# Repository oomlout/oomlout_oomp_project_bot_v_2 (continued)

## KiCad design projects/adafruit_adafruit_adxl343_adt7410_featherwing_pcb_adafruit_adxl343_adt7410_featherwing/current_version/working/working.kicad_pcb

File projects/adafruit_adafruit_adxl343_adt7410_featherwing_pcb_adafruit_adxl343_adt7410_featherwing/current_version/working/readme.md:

# adafruit_adxl343_adt7410_featherwing_pcb
 
## summary 
* id: adafruit_adafruit_adxl343_adt7410_featherwing_pcb_adafruit_adxl343_adt7410_featherwing
* user: adafruit
* name: adafruit_adxl343_adt7410_featherwing_pcb
* board: adafruit_adxl343_adt7410_featherwing
* repo: https://github.com/adafruit/Adafruit-ADXL343-ADT7410-Featherwing-PCB

* src_file_repo_sch: 
* src_file_repo_sch_link: https://github.com/adafruit/Adafruit-ADXL343-ADT7410-Featherwing-PCB/tree/master/
* full details link: https://github.com/oomlout/oomlout_oomp_project_bot_v_2/tree/main/projects/adafruit_adafruit_adxl343_adt7410_featherwing_pcb_adafruit_adxl343_adt7410_featherwing/current_version/working  

## schematic  
  
[schematic (pdf)](working_schematic.pdf) 

## pcb  

[board (pdf)](working.pdf)  

## working_bom
| Id | Designator | Footprint | Quantity | Designation | Supplier and ref |  | None | 
| --- | --- | --- | --- | --- | --- | --- | --- | 
| 1 | U$24 | ADIWING_TOP | 1 |  |  |  | [''] | 
| 2 | JP4,JP1 | 1X02_ROUND | 2 |  |  |  | [''] | 
| 3 | FID2,FID1 | FIDUCIAL_1MM | 2 | FIDUCIAL_1MM |  |  | [''] | 
| 4 | U2 | LGA14 | 1 | ADXL343 |  |  | [''] | 
| 5 | SJ1,SJ3,SJ2 | SOLDERJUMPER_ARROW_NOPASTE | 3 |  |  |  | [''] | 
| 6 | U1 | SOIC8_150MIL | 1 | ADT7410 |  |  | [''] | 
| 7 | R9,R4,R6,R3,R2,R1,R5,R8,R7 | 0603-NO | 9 | 10K |  |  | [''] | 
| 8 | C1,C3 | 0603-NO | 2 | 0.1uF |  |  | [''] | 
| 9 | C2 | 0805-NO | 1 | 10uF |  |  | [''] | 
| 10 | JP3 | 1X16_ROUND_76MIL | 1 |  |  |  | [''] | 
| 11 | JP2 | 1X12_ROUND_76MIL | 1 |  |  |  | [''] | 
| 12 | MS1 | FEATHERWING | 1 | FEATHERWING |  |  | [''] | 
| 13 | U$23 | FEATHERLOGO_MED | 1 |  |  |  | [''] | 
| 14 | U$1 | PCBFEAT-REV-040 | 1 |  |  |  | [''] | 

## bom_schematic
| Ref | Qnty | Value | Cmp name | Footprint | Description | Vendor | DNP | 
| --- | --- | --- | --- | --- | --- | --- | --- | 
| C1, C3 | 2 | 0.1uF | CAP_CERAMIC0603_NO | working:0603-NO |  |  |  | 
| C2 | 1 | 10uF | CAP_CERAMIC0805-NOOUTLINE | working:0805-NO |  |  |  | 
| FID1, FID2 | 2 | FIDUCIAL_1MM | FIDUCIAL_1MM | working:FIDUCIAL_1MM |  |  |  | 
| JP1, JP4 | 2 | HEADER-1X2ROUND | HEADER-1X2ROUND | working:1X02_ROUND |  |  |  | 
| JP2 | 1 | HEADER-1X1276MIL | HEADER-1X1276MIL | working:1X12_ROUND_76MIL |  |  |  | 
| JP3 | 1 | HEADER-1X16_76MIL | HEADER-1X16_76MIL | working:1X16_ROUND_76MIL |  |  |  | 
| MS1 | 1 | FEATHERWING | FEATHERWING | working:FEATHERWING |  |  |  | 
| R1, R2, R3, R4, R5, R6, R7, R8, R9 | 9 | 10K | RESISTOR_0603_NOOUT | working:0603-NO |  |  |  | 
| SJ1, SJ2, SJ3 | 3 | SOLDERJUMPER | SOLDERJUMPER | working:SOLDERJUMPER_ARROW_NOPASTE |  |  |  | 
| U1 | 1 | ADT7410 | TEMP_ADT7410 | working:SOIC8_150MIL |  |  |  | 
| U2 | 1 | ADXL343 | ACCEL_ADXL343 | working:LGA14 |  |  |  |

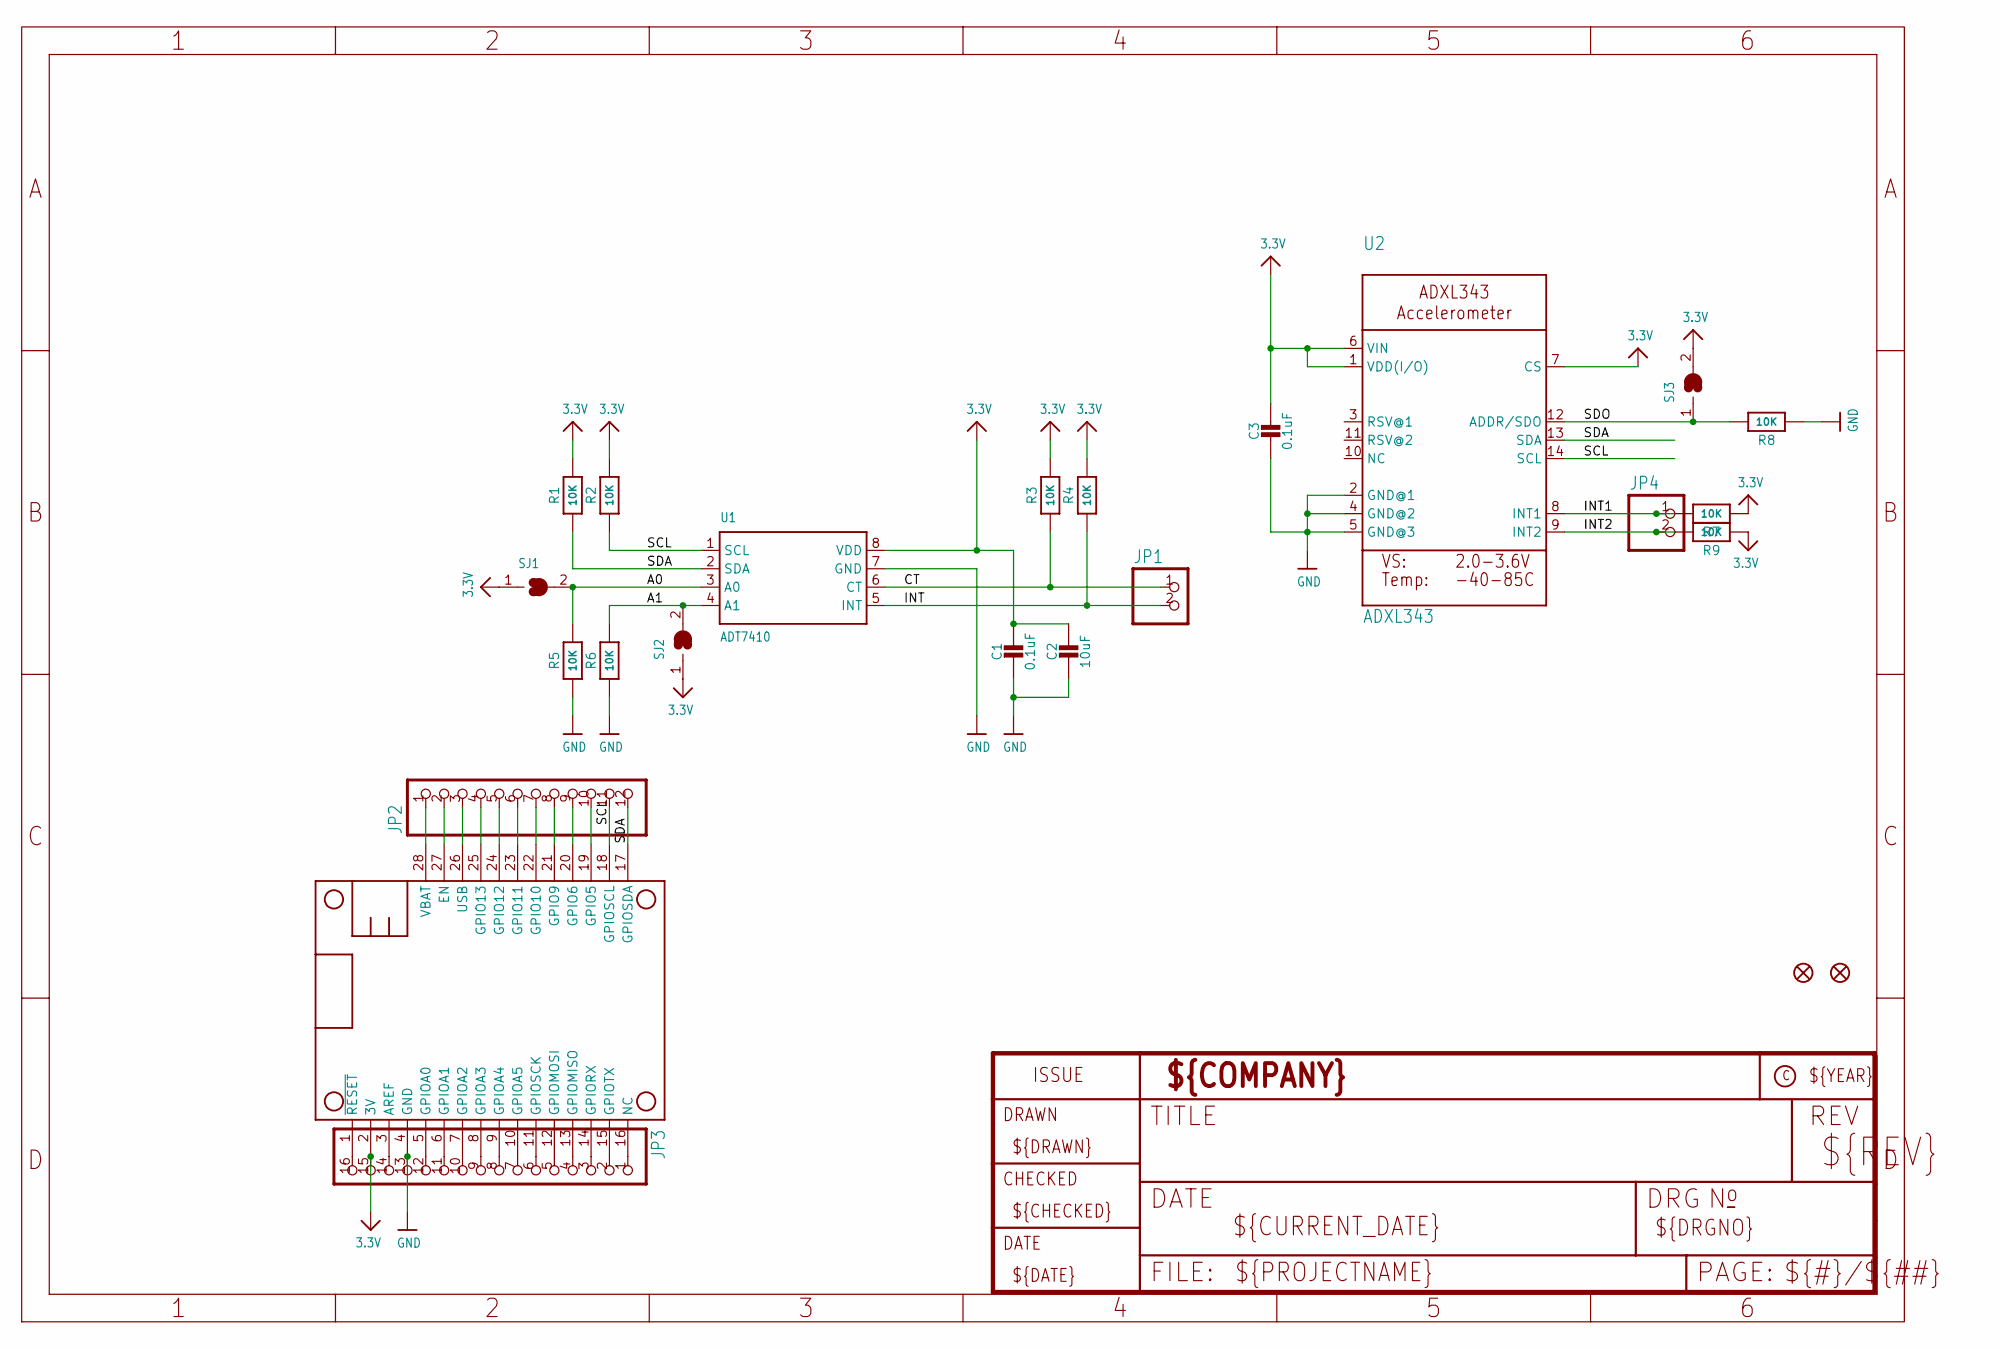
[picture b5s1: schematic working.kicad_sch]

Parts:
C1, C3: 0.1uF; 0603-NO
C2: 10uF; 0805-NO
FID1, FID2: FIDUCIAL_1MM
JP1, JP4: HEADER-1X2ROUND; 1X02_ROUND
JP2: HEADER-1X1276MIL; 1X12_ROUND_76MIL
JP3: HEADER-1X16_76MIL; 1X16_ROUND_76MIL
MS1: FEATHERWING
R1, R2, R3, R4, R5, R6, R7, R8, R9: 10K; 0603-NO
SJ1, SJ2, SJ3: SOLDERJUMPER; SOLDERJUMPER_ARROW_NOPASTE
U1: ADT7410; SOIC8_150MIL
U2: ADXL343; LGA14

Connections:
3.3V: C1.1, C2.1, C3.1, JP3.15, MS1.2 (3V), R1.2, R2.2, R3.2, R4.2, R7.1, R9.1, SJ1.1, SJ2.1, SJ3.2, U1.8 (VDD), U2.1 (VDD(I/O)), U2.6 (VIN), U2.7 (CS)
A0: R5.2, SJ1.2, U1.3 (A0)
A1: R6.2, SJ2.2, U1.4 (A1)
CT: JP1.1, R3.1, U1.6 (CT)
GND: C1.2, C2.2, C3.2, JP3.13, MS1.4 (GND), R5.1, R6.1, R8.1, U1.7 (GND), U2.2 (GND@1), U2.4 (GND@2), U2.5 (GND@3)
INT: JP1.2, R4.1, U1.5 (INT)
INT1: JP4.1, R7.2, U2.8 (INT1)
INT2: JP4.2, R9.2, U2.9 (INT2)
unnamed: JP2.2, MS1.27 (EN)
unnamed: JP2.4, MS1.25 (GPIO13)
unnamed: JP2.5, MS1.24 (GPIO12)
unnamed: JP2.6, MS1.23 (GPIO11)
unnamed: JP2.7, MS1.22 (GPIO10)
unnamed: JP2.8, MS1.21 (GPIO9)
unnamed: JP2.9, MS1.20 (GPIO6)
unnamed: JP2.10, MS1.19 (GPIO5)
unnamed: JP3.1, MS1.16 (NC)
unnamed: JP3.2, MS1.15 (GPIOTX)
unnamed: JP3.3, MS1.14 (GPIORX)
unnamed: JP3.4, MS1.13 (GPIOMISO)
unnamed: JP3.5, MS1.12 (GPIOMOSI)
unnamed: JP3.6, MS1.11 (GPIOSCK)
unnamed: JP3.7, MS1.10 (GPIOA5)
unnamed: JP3.8, MS1.9 (GPIOA4)
unnamed: JP3.9, MS1.8 (GPIOA3)
unnamed: JP3.10, MS1.7 (GPIOA2)
unnamed: JP3.11, MS1.6 (GPIOA1)
unnamed: JP3.12, MS1.5 (GPIOA0)
unnamed: JP3.14, MS1.3 (AREF)
unnamed: JP3.16, MS1.1 (~RESET)
SCL: JP2.11, MS1.18 (GPIOSCL), R2.1, U1.1 (SCL), U2.14 (SCL)
SDA: JP2.12, MS1.17 (GPIOSDA), R1.1, U1.2 (SDA), U2.13 (SDA)
SDO: R8.2, SJ3.1, U2.12 (ADDR/SDO)
USB: JP2.3, MS1.26 (USB)
VBAT: JP2.1, MS1.28 (VBAT)

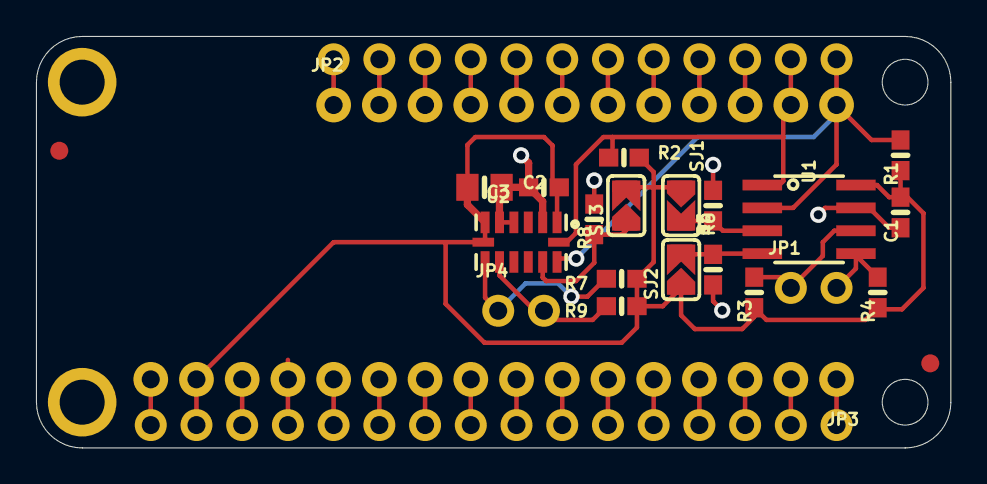
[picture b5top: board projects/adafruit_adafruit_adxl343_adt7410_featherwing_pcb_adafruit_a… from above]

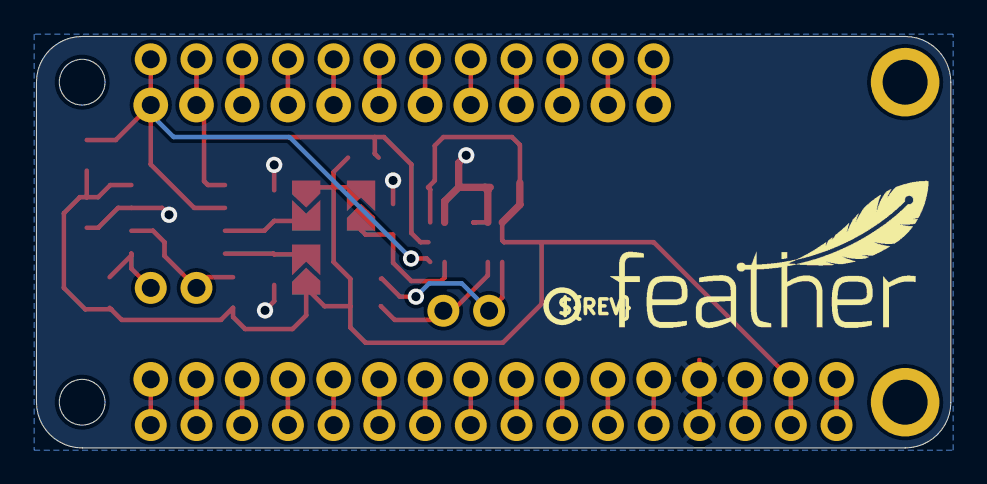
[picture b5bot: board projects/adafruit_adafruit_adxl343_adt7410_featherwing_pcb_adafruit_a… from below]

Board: 2 copper layers, 50.8 x 22.9 mm, 27 parts (2 on the bottom side), 35 nets.

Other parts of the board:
U$1: PCBFEAT-REV-040
U$23: FEATHERLOGO_MED
U$24: ADIWING_TOP

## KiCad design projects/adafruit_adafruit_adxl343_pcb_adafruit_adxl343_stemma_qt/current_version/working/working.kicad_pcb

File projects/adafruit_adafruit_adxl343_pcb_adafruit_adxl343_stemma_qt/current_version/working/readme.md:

# adafruit_adxl343_pcb
 
## summary 
* id: adafruit_adafruit_adxl343_pcb_adafruit_adxl343_stemma_qt
* user: adafruit
* name: adafruit_adxl343_pcb
* board: adafruit_adxl343_stemma_qt
* repo: https://github.com/adafruit/Adafruit_ADXL343_PCB

* src_file_repo_sch: 
* src_file_repo_sch_link: https://github.com/adafruit/Adafruit_ADXL343_PCB/tree/master/
* full details link: https://github.com/oomlout/oomlout_oomp_project_bot_v_2/tree/main/projects/adafruit_adafruit_adxl343_pcb_adafruit_adxl343_stemma_qt/current_version/working  

## schematic  
  
[schematic (pdf)](working_schematic.pdf) 

## pcb  

[board (pdf)](working.pdf)  

## working_bom
| Id | Designator | Footprint | Quantity | Designation | Supplier and ref |  | None | 
| --- | --- | --- | --- | --- | --- | --- | --- | 
| 1 | U$4,U$11 | ADAFRUIT_3.5MM | 2 |  |  |  | [''] | 
| 2 | JP2 | 1X04_ROUND | 1 |  |  |  | [''] | 
| 3 | U2 | SOT23-5 | 1 | AP2112K-3.3 |  |  | [''] | 
| 4 | FID3,FID4 | FIDUCIAL_1MM | 2 | FIDUCIAL_1MM |  |  | [''] | 
| 5 | JP1 | 1X06_ROUND_70 | 1 |  |  |  | [''] | 
| 6 | C2 | _0805MP | 1 | 10uF |  |  | [''] | 
| 7 | R3,R1 | RESPACK_4X0603 | 2 | 10K |  |  | [''] | 
| 8 | D1 | CHIPLED_0603_NOOUTLINE | 1 | GREEN |  |  | [''] | 
| 9 | C3 | 0805-NO | 1 | 10uF |  |  | [''] | 
| 10 | U$21,U$19,U$1,U$17 | MOUNTINGHOLE_2.5_PLATED | 4 | MOUNTINGHOLE2.5 |  |  | [''] | 
| 11 | CONN3,CONN4 | JST_SH4 | 2 | STEMMA_I2C_QT |  |  | [''] | 
| 12 | C1 | 0603-NO | 1 | 0.1uF |  |  | [''] | 
| 13 | D2 | SOD-323 | 1 | 1N4148 |  |  | [''] | 
| 14 | Q2 | SOT363 | 1 | BSS138 |  |  | [''] | 
| 15 | U1 | LGA14 | 1 | ADXL343 |  |  | [''] | 
| 16 | U$30,U$31 | STEMMAQT | 2 |  |  |  | [''] | 
| 17 | SJ1 | SOLDERJUMPER_CLOSEDWIRE | 1 |  |  |  | [''] | 
| 18 | U$25 | PCBFEAT-REV-040 | 1 |  |  |  | [''] | 

## bom_schematic
| Ref | Qnty | Value | Cmp name | Footprint | Description | Vendor | DNP | 
| --- | --- | --- | --- | --- | --- | --- | --- | 
| C1 | 1 | 0.1uF | CAP_CERAMIC0603_NO | working:0603-NO |  |  |  | 
| C2 | 1 | 10uF | CAP_CERAMIC_0805MP | working:_0805MP |  |  |  | 
| C3 | 1 | 10uF | CAP_CERAMIC0805-NOOUTLINE | working:0805-NO |  |  |  | 
| CONN3, CONN4 | 2 | STEMMA_I2C_QT | STEMMA_I2C_QT | working:JST_SH4 |  |  |  | 
| D1 | 1 | GREEN | LED0603_NOOUTLINE | working:CHIPLED_0603_NOOUTLINE |  |  |  | 
| D2 | 1 | 1N4148 | DIODESOD-323 | working:SOD-323 |  |  |  | 
| FID3, FID4 | 2 | FIDUCIAL_1MM | FIDUCIAL_1MM | working:FIDUCIAL_1MM |  |  |  | 
| JP1 | 1 | HEADER-1X670MIL | HEADER-1X670MIL | working:1X06_ROUND_70 |  |  |  | 
| JP2 | 1 | HEADER-1X4ROUND | HEADER-1X4ROUND | working:1X04_ROUND |  |  |  | 
| Q2 | 1 | BSS138 | MOSFET-N_DUAL | working:SOT363 |  |  |  | 
| R1, R3 | 2 | 10K | RESISTOR_4PACK | working:RESPACK_4X0603 |  |  |  | 
| SJ1 | 1 | SOLDERJUMPERCLOSED | SOLDERJUMPERCLOSED | working:SOLDERJUMPER_CLOSEDWIRE |  |  |  | 
| U1 | 1 | ADXL343 | ACCEL_ADXL343 | working:LGA14 |  |  |  | 
| U2 | 1 | AP2112K-3.3 | VREG_SOT23-5 | working:SOT23-5 |  |  |  | 
| U$1, U$17, U$19, U$21 | 4 | MOUNTINGHOLE2.5 | MOUNTINGHOLE2.5 | working:MOUNTINGHOLE_2.5_PLATED |  |  |  | 

## mounting_holes
| x | y | package | value | ref | size | 
| --- | --- | --- | --- | --- | --- | 
| 0.0 | 12.7 | MOUNTINGHOLE_2.5_PLATED | MOUNTINGHOLE2.5 | U$1 | m3 | 
| 20.32 | 12.7 | MOUNTINGHOLE_2.5_PLATED | MOUNTINGHOLE2.5 | U$17 | m3 | 
| 0.0 | 0.0 | MOUNTINGHOLE_2.5_PLATED | MOUNTINGHOLE2.5 | U$19 | m3 | 
| 20.32 | 0.0 | MOUNTINGHOLE_2.5_PLATED | MOUNTINGHOLE2.5 | U$21 | m3 |

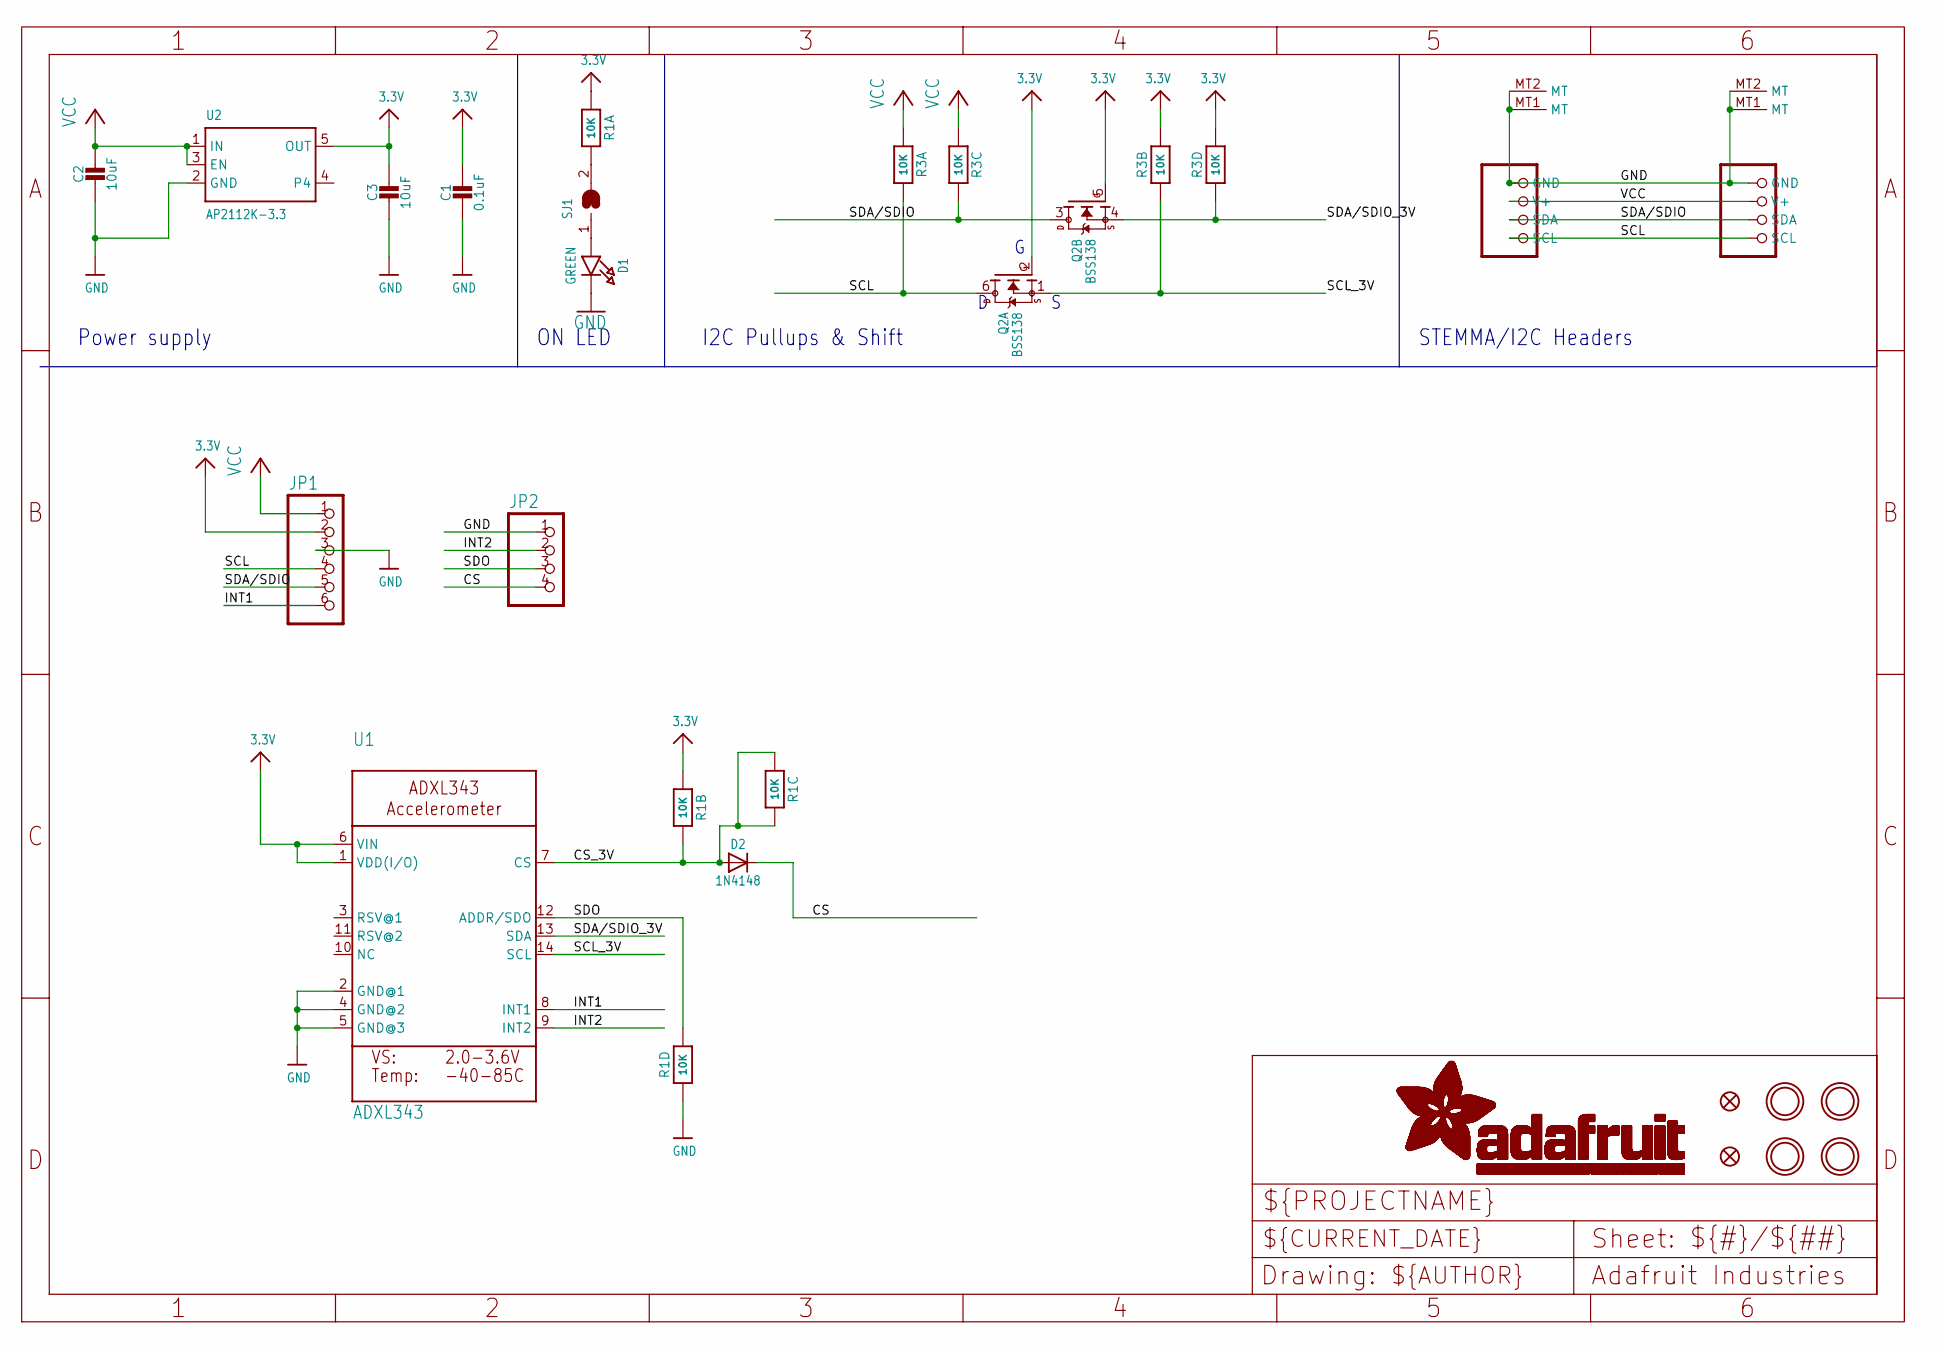
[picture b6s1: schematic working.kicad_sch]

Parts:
C1: 0.1uF; 0603-NO
C2: 10uF; _0805MP
C3: 10uF; 0805-NO
CONN3, CONN4: STEMMA_I2C_QT; JST_SH4
D1: GREEN; CHIPLED_0603_NOOUTLINE
D2: 1N4148; SOD-323
FID3, FID4: FIDUCIAL_1MM
JP1: HEADER-1X670MIL; 1X06_ROUND_70
JP2: HEADER-1X4ROUND; 1X04_ROUND
Q2: BSS138; SOT363
R1, R3: 10K; RESPACK_4X0603
SJ1: SOLDERJUMPERCLOSED; SOLDERJUMPER_CLOSEDWIRE
U1: ADXL343; LGA14
U2: AP2112K-3.3; SOT23-5
U$1, U$17, U$19, U$21: MOUNTINGHOLE2.5; MOUNTINGHOLE_2.5_PLATED

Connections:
3.3V: C1.1, C3.1, JP1.2, Q2.2 (G), Q2.5 (G), R1.1, R1.2 (1), R3.2 (1), R3.4 (1), U1.1 (VDD(I/O)), U1.6 (VIN), U2.5 (OUT)
CS: D2.C, JP2.4
CS_3V: D2.A, R1.3 (1), R1.6 (2), R1.7 (2), U1.7 (CS)
GND: C1.2, C2.2, C3.2, CONN3.1 (GND), CONN3.MT1 (MT), CONN3.MT2 (MT), CONN4.1 (GND), CONN4.MT1 (MT), CONN4.MT2 (MT), D1.C, JP1.3, JP2.1, R1.4 (1), U1.2 (GND@1), U1.4 (GND@2), U1.5 (GND@3), U2.2 (GND)
INT1: JP1.6, U1.8 (INT1)
INT2: JP2.2, U1.9 (INT2)
unnamed: R1.8 (2), SJ1.2
unnamed: D1.A, SJ1.1
SCL: CONN3.4 (SCL), CONN4.4 (SCL), JP1.4, Q2.6 (D), R3.8 (2)
SCL_3V: Q2.1 (S), R3.7 (2), U1.14 (SCL)
SDA/SDIO: CONN3.3 (SDA), CONN4.3 (SDA), JP1.5, Q2.3 (D), R3.6 (2)
SDA/SDIO_3V: Q2.4 (S), R3.5 (2), U1.13 (SDA)
SDO: JP2.3, R1.5 (2), U1.12 (ADDR/SDO)
VCC: C2.1, CONN3.2 (V+), CONN4.2 (V+), JP1.1, R3.1, R3.3 (1), U2.1 (IN), U2.3 (EN)

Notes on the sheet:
STEMMA/I2C Headers
I2C Pullups & Shift
ON LED
Power supply

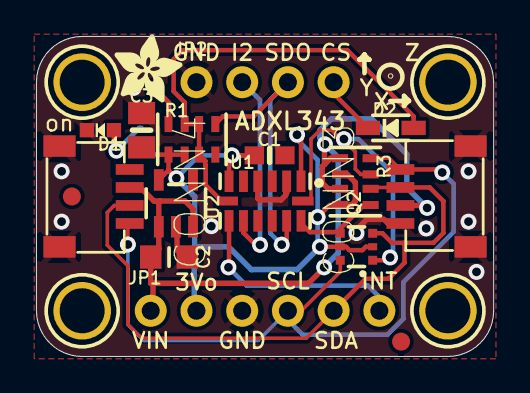
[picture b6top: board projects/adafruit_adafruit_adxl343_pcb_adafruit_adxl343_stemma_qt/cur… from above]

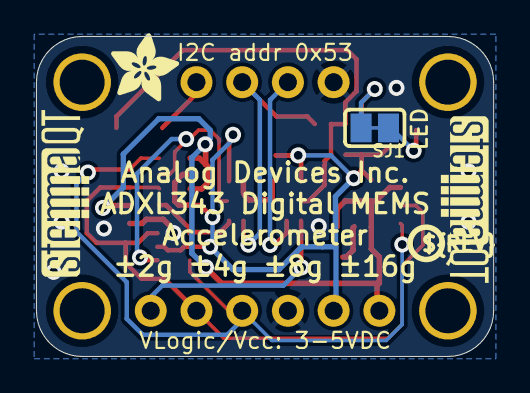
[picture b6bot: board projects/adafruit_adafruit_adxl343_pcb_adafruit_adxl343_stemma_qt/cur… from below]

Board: 2 copper layers, 25.4 x 17.8 mm, 26 parts (5 on the bottom side), 14 nets.

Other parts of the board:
U$4, U$11: ADAFRUIT_3.5MM
U$25: PCBFEAT-REV-040
U$30, U$31: STEMMAQT
